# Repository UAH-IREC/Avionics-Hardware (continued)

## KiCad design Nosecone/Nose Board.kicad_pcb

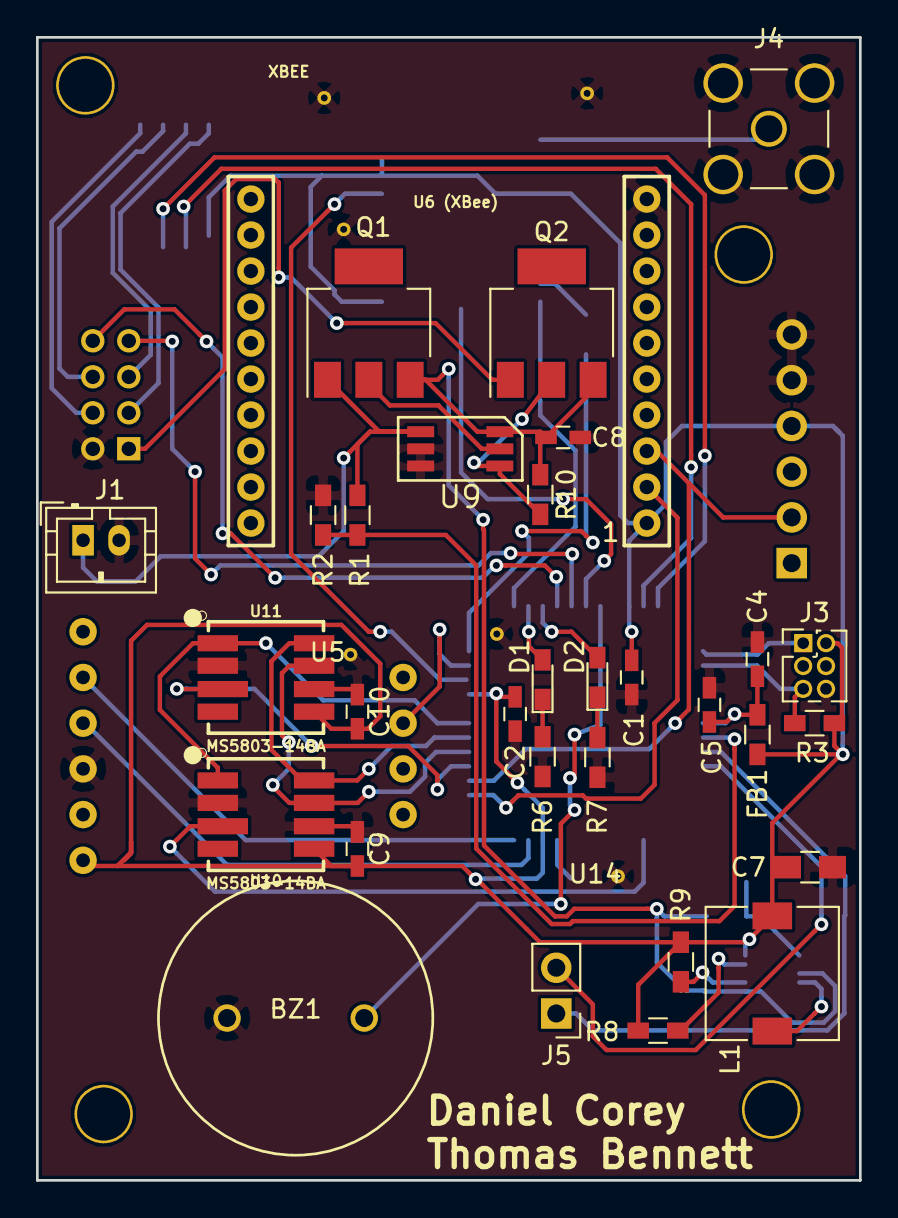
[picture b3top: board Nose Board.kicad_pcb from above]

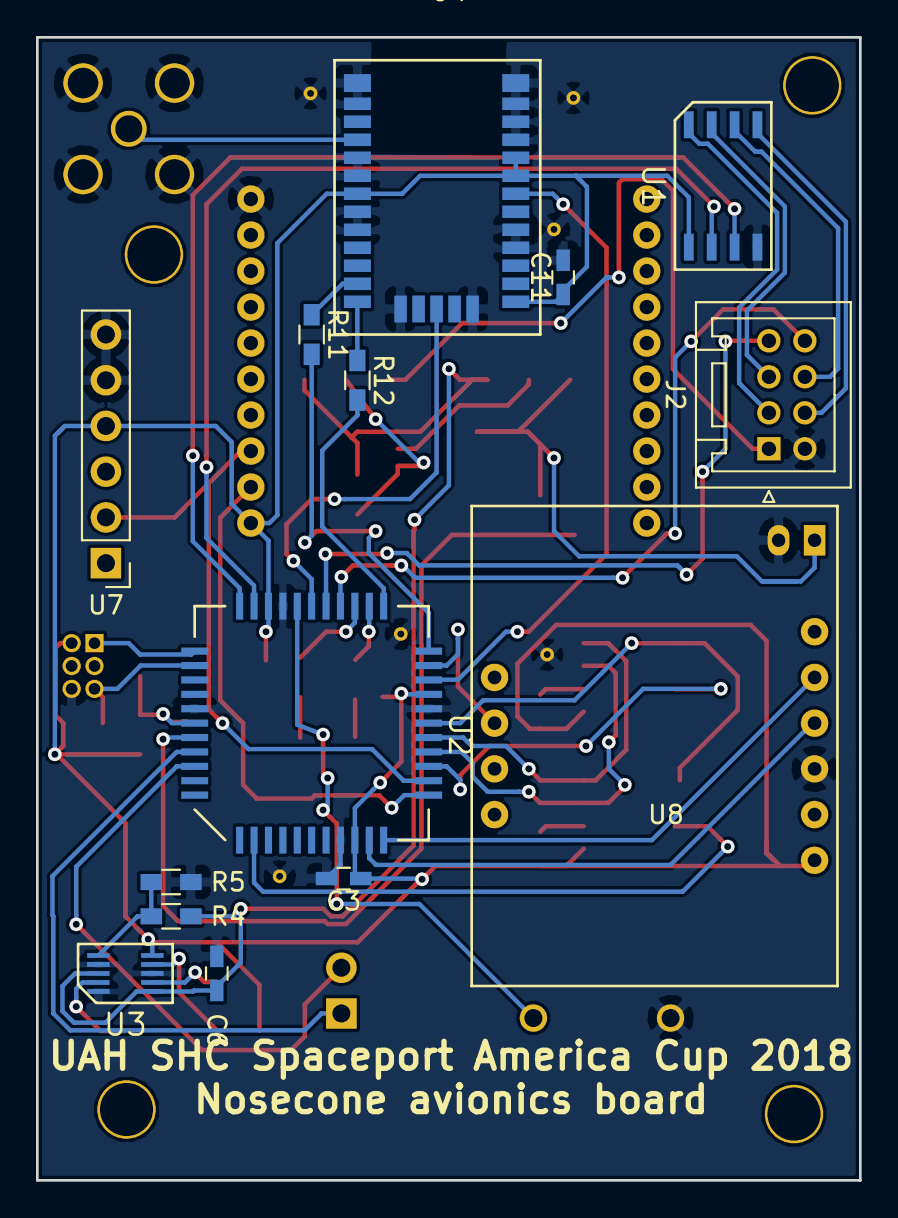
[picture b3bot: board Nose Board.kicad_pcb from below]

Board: 2 copper layers, 45.7 x 63.5 mm, 47 parts (14 on the bottom side), 47 nets.

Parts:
BZ1: Buzzer; Buzzer-CUI_CEP-2242
C1, C2, C3, C5, C9, C10: 100nF; C_0603_HandSoldering
C4, C6: 10uF; C_0603_HandSoldering
C7: 22uF; C_0805_HandSoldering
C8: 22uF; C_0603_HandSoldering
C11: 4.7uF; C_0603_HandSoldering
D1, D2: LED; LED_0603_HandSoldering
FB1: FERRITE_BEAD-0603; L_0603_HandSoldering
J1: Conn_01x02; JST_PH_B2B-PH-K_02x2.00mm_Straight
J2: Conn_02x04_Odd_Even; JST_PUD_B08B-PUDSS_2x04x2.00mm_Straight
J3: Conn_02x03_Odd_Even; Pin_Header_Straight_2x03_Pitch1.27mm
J4: Conn_Coaxial; SMA_THT_Jack_Straight
J5: Conn_01x02; Pin_Header_Straight_1x02_Pitch2.54mm
L1: 10uH; L_7.3x7.3_H4.5
Q1, Q2: Q_PMOS_DGS; SOT-223-3_TabPin2
R1: 90.9k; R_0603_HandSoldering
R2, R3: 10k; R_0603_HandSoldering
R4: 130k; R_0603_HandSoldering
R5: 100k; R_0603_HandSoldering
R6, R7, R11, R12: 220; R_0603_HandSoldering
R8, R9: 1M; R_0603_HandSoldering
R10: 470k; R_0603_HandSoldering
U1: RS485_converter_ISL83488; SOIC-8
U2: ATXMEGA16A4U-AU; QFP_44
U3: 3.3V_DCDC_Conv_TPS62056DGS; SOIC-10
U4: GPS_UBX_CAM_M8C; UBX_CAM-M8C
U5, U14: Via-stitch; Small-via
U6 (XBee): XBEE
U7: OpenLog; Pin_Header_Straight_1x06_Pitch2.54mm
U8: BNO055; BNO055_Breakout
U9: LTC4412; SOIC-6
U10, U11: MS5803-14BA; MS5803

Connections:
+3V3: C1.2, C2.1, C3.1, C7.1, C9.2, C10.2, C11.1, FB1.1, J3.2, L1.1, R3.1, R8.1, R9.1, U1.1, U2.9, U2.19, U2.31, U3.5, U4.1, U4.8, U4.9, U4.20, U6 (XBee).1, U7.4, U8.1, U10.5, U11.5
+BATT: J1.1, Q1.1, R1.1, U9.1
/A1: J5.1, U2.41
/A2: J5.2, U2.42
/Buzzer_drive: BZ1.1, U2.29
/Center_Din: U1.3, U2.33
/Center_Dout: U1.2, U2.32
/Debug_RX: J2.8, U2.26
/Debug_TX: J2.7, U2.27
/GPS1_EXTINT: U2.20, U4.7
/GPS1_PPS: U2.28, U4.29
/GPS1_RXD: R12.2, U2.23
/GPS1_TXD: R11.2, U2.22
/IMU_INT: U2.21, U8.8
/IMU_SCL: U2.11, U8.5
/IMU_SDA: U2.10, U8.4
/LED_STATUS1: D1.2, U2.24
/LED_STATUS2: D2.2, U2.25
/P1_CS: U2.14, U11.3
/P2_CS: U2.2, U10.3
/PDI_CLK: J3.5, R3.2, U2.35
/PDI_Data: J3.1, U2.34
/P_MISO: U2.16, U10.8, U11.8
/P_MOSI: U2.15, U10.7, U11.7
/P_SCLK: U2.17, U10.1, U11.1
/RS422in+: J2.6, U1.6
/RS422in-: J2.4, U1.5
/RS422out+: J2.3, U1.8
/RS422out-: J2.5, U1.7
/Vbatt_meas: R1.2, R2.1, U2.40
/XBEE_Din: U2.13, U6 (XBee).3, U7.2
/XBEE_Dout: U2.12, U6 (XBee).2
GND: BZ1.2, C1.1, C2.2, C3.2, C4.1, C5.1, C6.2, C7.2, C8.2, C9.1, C10.1, C11.2, J1.2, J2.2, J3.6, J4.2, R2.2, R5.2, R6.1, R7.1, U1.4, U2.8, U2.18, U2.30, U2.38, U3.3, U3.7, U3.10, U4.4, U4.5, U4.10, U4.11, U4.12, U4.13, U4.14, U4.15, U4.18, U4.19, U4.21, U4.22, U4.27, U4.31, U5.1, U6 (XBee).10, U7.5, U7.6, U8.3, U9.2, U9.3, U10.2, U10.6, U11.2, U11.6, U14.1
unnamed: C4.2, C5.2, FB1.2, U2.39
unnamed: D1.1, R6.2
unnamed: D2.1, R7.2
unnamed: J4.1, U4.17
unnamed: L1.2, U3.9
unnamed: Q1.2, U9.5
unnamed: Q2.2, R10.2, U9.4
unnamed: R4.2, R5.1, U3.6
unnamed: R8.2, U3.4
unnamed: R9.2, U3.2
unnamed: R11.1, U4.25
unnamed: R12.1, U4.26
VBUS: J2.1, Q2.1
VDC: C6.1, C8.1, Q1.3, Q2.3, R4.1, R10.1, U3.1, U3.8, U9.6

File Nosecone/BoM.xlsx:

Ref | Value | Footprint | Description | Vendor Part Number | Link
BZ1 | Buzzer | Misc components:Buzzer-CUI_CEP-2242 | AUDIO PIEZO INDICATOR 3-16V TH |  | https://www.digikey.com/product-detail/en/cui-inc/CEP-2242/1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
C1 | 100nF | Capacitors_SMD:C_0603_HandSoldering | CAP CER 0.1UF 50V X7R 0603 | 399-7845-1-ND | https://www.digikey.com/product-detail/en/kemet/C0603C104M5R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
C2 | 100nF | Capacitors_SMD:C_0603_HandSoldering | CAP CER 0.1UF 50V X7R 0604 | 399-7845-1-ND | https://www.digikey.com/product-detail/en/kemet/C0603C104M5R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
C3 | 100nF | Capacitors_SMD:C_0603_HandSoldering | CAP CER 0.1UF 50V X7R 0605 | 399-7845-1-ND | https://www.digikey.com/product-detail/en/kemet/C0603C104M5R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
C4 | 10uF | Capacitors_SMD:C_0603_HandSoldering | CAP CER 10UF 35V X5R 0603 | 490-13248-1-ND | https://www.digikey.com/product-detail/en/murata-electronics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
C5 | 100nF | Capacitors_SMD:C_0603_HandSoldering | CAP CER 0.1UF 50V X7R 0605 | 399-7845-1-ND | https://www.digikey.com/product-detail/en/kemet/C0603C104M5R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
C6 | 10uF | Capacitors_SMD:C_0603_HandSoldering | CAP CER 10UF 35V X5R 0603 | 490-13248-1-ND | https://www.digikey.com/product-detail/en/murata-electronics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
C7 | 22uF | Capacitors_SMD:C_0603_HandSoldering | CAP CER 22UF 25V X5R 0805 | 490-12389-1-ND | https://www.digikey.com/product-detail/en/murata-electronics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
C8 | 22uF | Capacitors_SMD:C_0603_HandSoldering | CAP CER 22UF 25V X5R 0805 | 490-12389-1-ND | https://www.digikey.com/product-detail/en/murata-electronics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
C9 | 100nF | Capacitors_SMD:C_0603_HandSoldering | CAP CER 0.1UF 50V X7R 0605 | 399-7845-1-ND | https://www.digikey.com/product-detail/en/kemet/C0603C104M5R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
C10 | 100nF | Capacitors_SMD:C_0603_HandSoldering | CAP CER 0.1UF 50V X7R 0605 | 399-7845-1-ND | https://www.digikey.com/product-detail/en/kemet/C0603C104M5R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
C11 | 4.7uF | Capacitors_SMD:C_0603_HandSoldering | CAP CER 4.7UF 25V X5R 0603 | 1276-1903-1-ND | https://www.digikey.com/product-detail/en/samsung-electro-me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
D1 | LED | LEDs:LED_0603_HandSoldering | LED GREEN CLEAR 0603 SMD | 160-1446-1-ND | https://www.digikey.com/product-detail/en/lite-on-inc/LTST-C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
D2 | LED | LEDs:LED_0603_HandSoldering | LED RED CLEAR 0603 SMD | 160-1447-1-ND | https://www.digikey.com/product-detail/en/lite-on-inc/LTST-C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
FB1 | FERRITE_BEAD-0603 | Inductors_SMD:L_0603_HandSoldering
J1 | Conn_01x02 | Connectors_JST:JST_PH_B2B-PH-K_02x2.00mm_Straight
J2 | Conn_02x04_Odd_Even | Connectors_JST:JST_PUD_B08B-PUDSS_2x04x2.00mm_Straight
J3 | Conn_02x03_Odd_Even | Pin_Headers:Pin_Header_Straight_2x03_Pitch1.27mm
J4 | Conn_Coaxial | Connectors:SMA_THT_Jack_Straight
J5 | Conn_01x02 | Pin_Headers:Pin_Header_Straight_1x02_Pitch2.54mm
L1 | 10uH | Inductors_SMD:L_7.3x7.3_H4.5
Q1 | Q_PMOS_DGS | TO_SOT_Packages_SMD:SOT-223-3_TabPin2 | MOSFET P-CH 60V 7A SOT223 | DMP6023LE-13DICT-ND | https://www.digikey.com/product-detail/en/diodes-incorporate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
Q2 | Q_PMOS_DGS | TO_SOT_Packages_SMD:SOT-223-3_TabPin2 | MOSFET P-CH 60V 7A SOT223 | DMP6023LE-13DICT-ND | https://www.digikey.com/product-detail/en/diodes-incorporate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
R1 | 10k | Resistors_SMD:R_0603_HandSoldering | RES SMD 10K OHM 5% 1/10W 0603 | 311-10KGRCT-ND | https://www.digikey.com/product-detail/en/yageo/RC0603JR-071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
R2 | 90.9k | Resistors_SMD:R_0603_HandSoldering | RES SMD 90.9K OHM 1% 1/10W 0603 | 311-90.9KHRCT-ND | https://www.digikey.com/product-detail/en/yageo/RC0603FR-079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
R3 | 10k | Resistors_SMD:R_0603_HandSoldering | RES SMD 10K OHM 5% 1/10W 0603 | 311-10KGRCT-ND | https://www.digikey.com/product-detail/en/yageo/RC0603JR-071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
R4 | 130k | Resistors_SMD:R_0603_HandSoldering | RES SMD 130K OHM 5% 1/10W 0603 | 311-130KGRCT-ND | https://www.digikey.com/product-detail/en/yageo/RC0603JR-071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
R5 | 100k | Resistors_SMD:R_0603_HandSoldering | RES SMD 100K OHM 5% 1/10W 0603 | CR0603-JW-104ELFCT-ND | https://www.digikey.com/product-detail/en/bourns-inc/CR0603-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
R6 | 220 | Resistors_SMD:R_0603_HandSoldering | RES SMD 220 OHM 5% 1/10W 0603 | 311-220GRCT-ND | https://www.digikey.com/product-detail/en/yageo/RC0603JR-072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
R7 | 220 | Resistors_SMD:R_0603_HandSoldering | RES SMD 220 OHM 5% 1/10W 0603 | 311-220GRCT-ND | https://www.digikey.com/product-detail/en/yageo/RC0603JR-072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
R8 | 1M | Resistors_SMD:R_0603_HandSoldering | RES SMD 1M OHM 1% 1/10W 0603 | 311-1.00MHRCT-ND | https://www.digikey.com/product-detail/en/yageo/RC0603FR-071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
R9 | 1M | Resistors_SMD:R_0603_HandSoldering | RES SMD 1M OHM 1% 1/10W 0604 | 311-1.00MHRCT-ND | https://www.digikey.com/product-detail/en/yageo/RC0603FR-071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
R10 | 470k | Resistors_SMD:R_0603_HandSoldering | RES SMD 470K OHM 5% 1/10W 0603 | 311-470KGRCT-ND | https://www.digikey.com/product-detail/en/yageo/RC0603JR-074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
R11 | 220 | Resistors_SMD:R_0603_HandSoldering | RES SMD 220 OHM 5% 1/10W 0603 | 311-220GRCT-ND | https://www.digikey.com/product-detail/en/yageo/RC0603JR-072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
R12 | 220 | Resistors_SMD:R_0603_HandSoldering | RES SMD 220 OHM 5% 1/10W 0603 | 311-220GRCT-ND | https://www.digikey.com/product-detail/en/yageo/RC0603JR-072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
U1 | RS485_converter_ISL83488 | Misc components:SOIC-8 | IC TXRX RS485/422 3.3V LP 8SOIC | ISL83488IBZ-TCT-ND | https://www.digikey.com/product-detail/en/intersil/ISL83488I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
U2 | ATXMEGA16A4U-AU | Misc components:QFP_44 | IC MCU 8BIT 128KB FLASH 44TQFP | ATXMEGA128A4U-AU-ND | https://www.digikey.com/product-detail/en/microchip-technolo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
U3 | 3.3V_DCDC_Conv_TPS62056DGS | Misc components:SOIC-10 | IC REG BCK 3.3V 0.8A SYNC 10MSOP | 296-27024-1-ND | https://www.digikey.com/product-detail/en/texas-instruments/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
U4 | GPS_UBX_CAM_M8C | Misc components:UBX_CAM-M8C | IC RECEIVER GPS CHIP ANT 31LCC | 672-1014-1-ND | https://www.digikey.com/product-detail/en/u-blox-america-inc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
U5 | Via-stitch | Misc components:Small-via | N/A | N/A | N/A
U6 | XBEE | RF:XBEE | 900 mHz SMA connector | Club stock (for now) | Club stock (for now)
U7 | OpenLog | Pin_Headers:Pin_Header_Straight_1x06_Pitch2.54mm | OPENLOG | 1568-1368-ND | https://www.digikey.com/products/en?mpart=DEV-13712&v=1568
U8 | BNO055 | Misc components:BNO055_Breakout | BREAKOUT BOARD 9-DOF IMU BNO055 | 1528-1426-ND | https://www.digikey.com/products/en?mpart=2472&v=1528
U9 | LTC4412 | Misc components:SOIC-6 | IC OR CTRLR SRC SELECT TSOT23-6 | LTC4412ES6#TRMPBFCT-ND | https://www.digikey.com/product-detail/en/linear-technology/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
U10 | MS5803-14BA | Silicon-Standard:MS5803 | MINIATURE ALTIMETER MODULE | 223-1626-5-ND | https://www.digikey.com/product-detail/en/te-connectivity-me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
U11 | MS5803-14BA | Silicon-Standard:MS5803 | MINIATURE ALTIMETER MODULE | 223-1626-5-ND | https://www.digikey.com/product-detail/en/te-connectivity-me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
U12 | Via-stitch | Misc components:Small-via | N/A | N/A | N/A
U13 | Via-stitch | Misc components:Small-via | N/A | N/A | N/A
N/A | GPS antenna |  |  |  | https://www.digikey.com/product-detail/en/taoglas-limited/AG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
N/A | UFL to SMA adapter
N/A | Breakaway pin headers 0.1" pitch
N/A | Xbee headers
N/A | Female pin headers 0.1" pitch

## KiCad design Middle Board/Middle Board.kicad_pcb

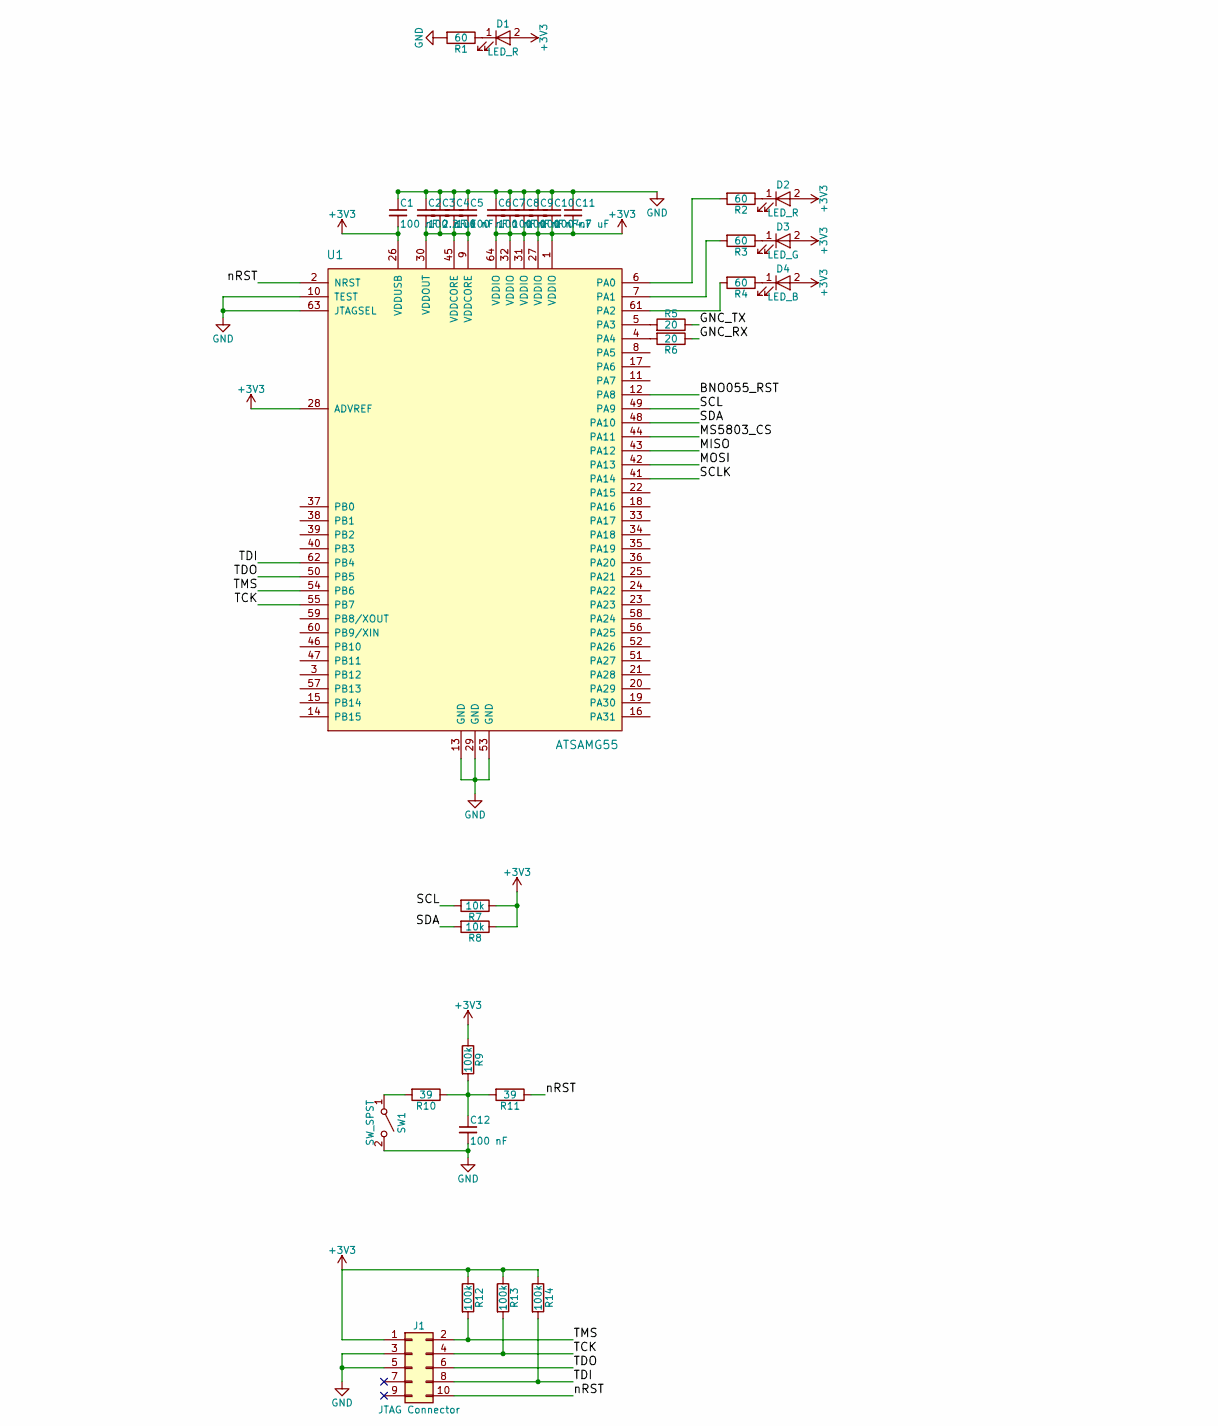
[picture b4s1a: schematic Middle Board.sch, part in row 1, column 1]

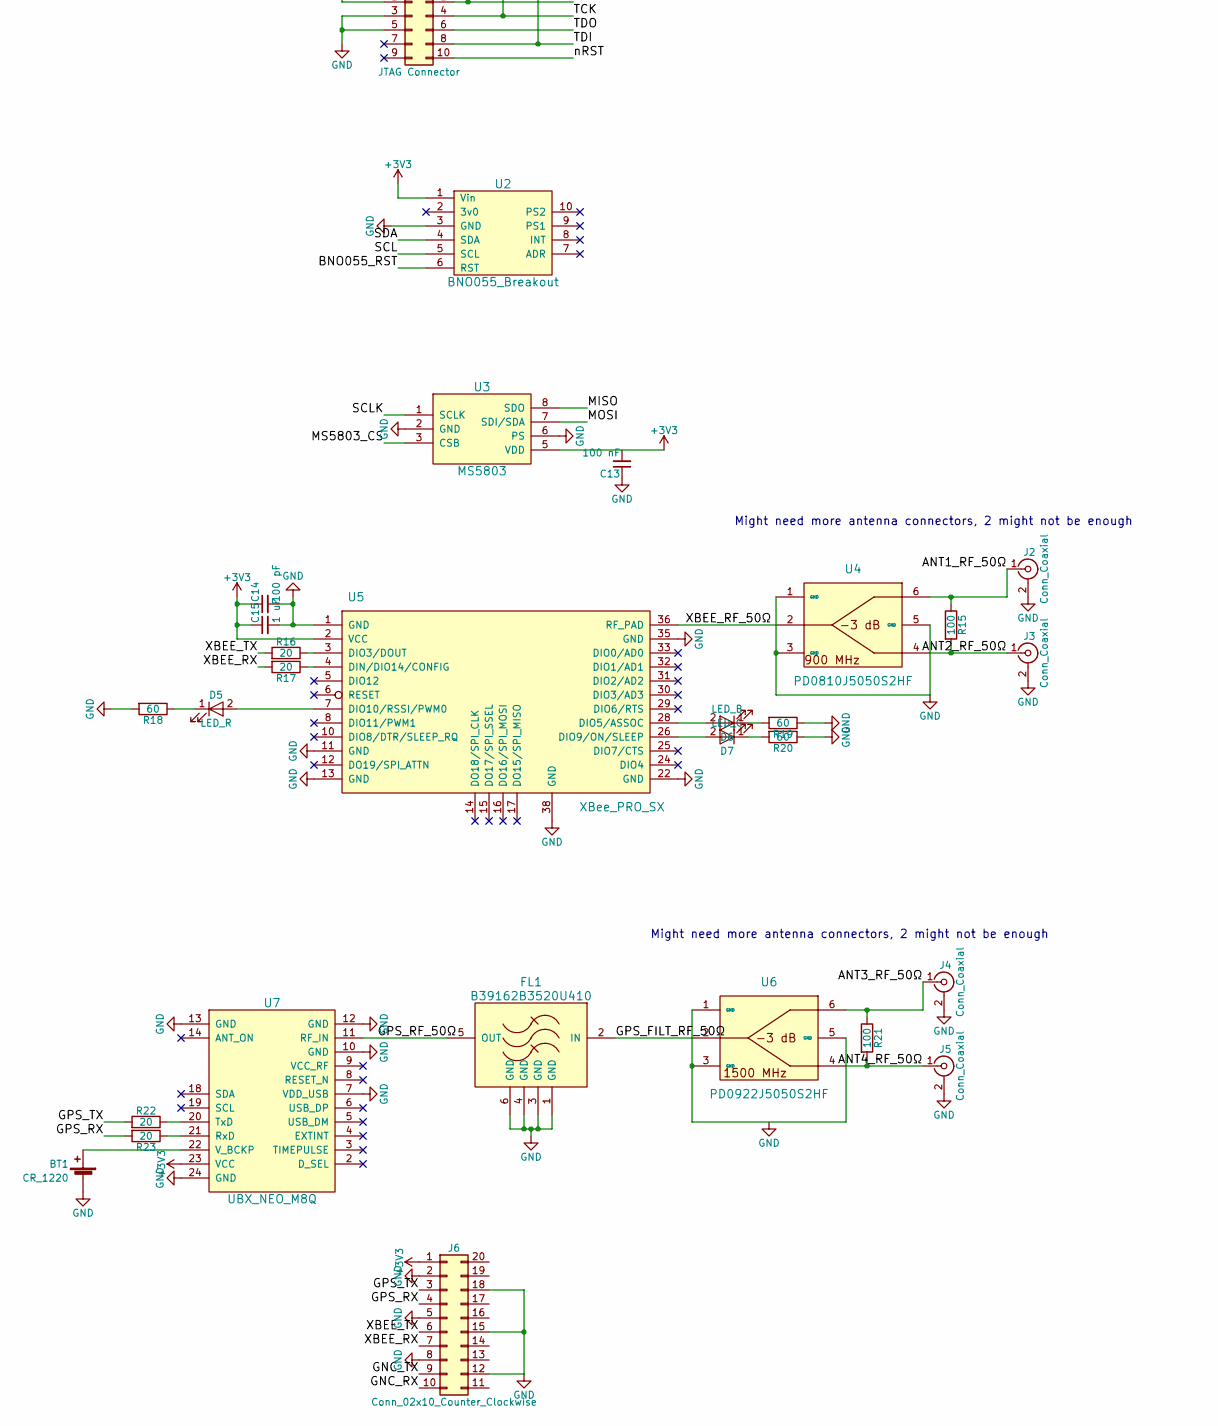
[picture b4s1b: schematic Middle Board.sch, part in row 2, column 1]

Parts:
BT1: CR_1220; Keystone_3000_1x12mm-CoinCell; Digikey Part Number 36-3000-ND
C1, C2, C4, C5, C6, C7, C8, C9, C10, C12, C13: 100 nF; C_0603; Digikey Part Number 490-1532-1-ND
C3: 2.2 uF; C_0603; Digikey Part Number 1276-1134-1-ND
C11: 4.7 uF; C_0805; Digikey Part Number 587-2990-6-ND
C14: 100 pF; C_0603; Digikey Part Number 1276-1909-6-ND
C15: 1 uF; C_0603; Digikey Part Number 1276-6524-1-ND
D1, D2, D5: LED_R; LED_0603_HandSoldering; Digikey Part Number 160-1436-1-ND
D3, D7: LED_G; LED_0603_HandSoldering; Digikey Part Number 160-1435-1-ND
D4, D6: LED_B; LED_0603_HandSoldering; Digikey Part Number 160-1647-1-ND
FL1: B39162B3520U410; Digikey Part Number 495-2363-6-ND
J1: JTAG Connector; 10_pin_Cortex-M_connector; Digikey Part Number SAM8799-ND
J2, J3, J4, J5: Conn_Coaxial; SMA_SMD_RIGHT_ANGLE; Digikey Part Number 931-1175-ND
J6: Conn_02x10_Counter_Clockwise; CONN_CARD_02x10_MALE; Digikey Part Number S3299-ND
R1, R2, R3, R4, R18, R19, R20: 60; R_0603; Digikey Part Number 311-56GRCT-ND
R5, R6, R16, R17, R22, R23: 20; R_0603; Digikey Part Number 311-20.0HRCT-ND
R7, R8: 10k; R_0603; Digikey Part Number 311-10.0KHRCT-ND
R9, R12, R13, R14: 100k; R_0603; Digikey Part Number 311-100KHRCT-ND
R10, R11: 39; R_0603; Digikey Part Number 311-39.0HRCT-ND
R15, R21: 100; R_0603; Digikey Part Number P100DBDKR-ND
SW1: SW_SPST; SW_SPST_SMD; Digikey Part Number CKN9112CT-ND
U1: ATSAMG55; LQFP-64_10x10mm_Pitch0.5mm; Digikey Part Number ATSAMG55J19B-AUTCT-ND
U2: BNO055_Breakout; Digikey Part Number 1528-1426-ND
U3: MS5803; Digikey Part Number 223-1623-5-ND
U4: PD0810J5050S2HF; SMD_PD_ANAREN; Digikey Part Number 1173-1093-1-ND
U5: XBee_PRO_SX; XBEE_PRO_SX; Digikey Part Number 602-1889-ND
U6: PD0922J5050S2HF; SMD_PD_ANAREN; Digikey Part Number 1173-1094-1-ND
U7: UBX_NEO_M8Q; Digikey Part Number 672-1009-1-ND

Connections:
+3V3: C1.2, C6.2, C7.2, C8.2, C9.2, C10.2, C11.2, C14.1, C15.1, D1.2 (A), D2.2 (A), D3.2 (A), D4.2 (A), J1.1, J6.1, R7.1, R8.1, R9.1, R12.1, R13.1, R14.1, U1.1 (VDDIO), U1.26 (VDDUSB), U1.27 (VDDIO), U1.28 (ADVREF), U1.31 (VDDIO), U1.32 (VDDIO), U1.64 (VDDIO), U2.1 (Vin), U3.5 (VDD), U5.2 (VCC), U7.23 (VCC)
/ANT1_RF_50Ω: J2.1 (In), R15.1, U4.6
/ANT2_RF_50Ω: J3.1 (In), R15.2, U4.4
/ANT3_RF_50Ω: J4.1 (In), R21.1, U6.6
/ANT4_RF_50Ω: J5.1 (In), R21.2, U6.4
/BNO055_RST: U1.12 (PA8), U2.6 (RST)
/GNC_RX: J6.10, R6.1
/GNC_TX: J6.9, R5.1
/GPS_FILT_RF_50Ω: FL1.2 (IN), U6.2
/GPS_RF_50Ω: FL1.5 (OUT), U7.11 (RF_IN)
/GPS_RX: J6.4, R23.2
/GPS_TX: J6.3, R22.2
/MISO: U1.43 (PA12), U3.8 (SDO)
/MOSI: U1.42 (PA13), U3.7 (SDI/SDA)
/MS5803_CS: U1.44 (PA11), U3.3 (CSB)
/SCL: R7.2, U1.49 (PA9), U2.5 (SCL)
/SCLK: U1.41 (PA14), U3.1 (SCLK)
/SDA: R8.2, U1.48 (PA10), U2.4 (SDA)
/TCK: J1.4, R13.2, U1.55 (PB7)
/TDI: J1.8, R14.2, U1.62 (PB4)
/TDO: J1.6, U1.50 (PB5)
/TMS: J1.2, R12.2, U1.54 (PB6)
/XBEE_RF_50Ω: U4.2, U5.36 (RF_PAD)
/XBEE_RX: J6.7, R17.2
/XBEE_TX: J6.6, R16.2
/nRST: J1.10, R11.1, U1.2 (NRST)
GND: BT1.2 (-), C1.1, C2.1, C3.1, C4.1, C5.1, C6.1, C7.1, C8.1, C9.1, C10.1, C11.1, C12.2, C13.1, C14.2, C15.2, FL1.1 (GND), FL1.3 (GND), FL1.4 (GND), FL1.6 (GND), J1.3, J1.5, J2.2 (Ext), J3.2 (Ext), J4.2 (Ext), J5.2 (Ext), J6.2, J6.5, J6.8, J6.12, J6.15, J6.18, R1.2, R18.2, R19.1, R20.1, SW1.2 (B), U1.10 (TEST), U1.13 (GND), U1.29 (GND), U1.53 (GND), U1.63 (JTAGSEL), U2.3 (GND), U3.2 (GND), U3.6 (PS), U4.1 (GND), U4.3 (GND), U4.5 (GND), U5.1 (GND), U5.11 (GND), U5.13 (GND), U5.22 (GND), U5.35 (GND), U5.38 (GND), U6.1 (GND), U6.3 (GND), U6.5 (GND), U7.7 (VDD_USB), U7.10 (GND), U7.12 (GND), U7.13 (GND), U7.24 (GND)
unnamed: BT1.1 (+), U7.22 (V_BCKP)
unnamed: C2.2, C3.2, C4.2, C5.2, U1.9 (VDDCORE), U1.30 (VDDOUT), U1.45 (VDDCORE)
unnamed: C12.1, R9.2, R10.1, R11.2
unnamed: D1.1 (K), R1.1
unnamed: D2.1 (K), R2.1
unnamed: D3.1 (K), R3.1
unnamed: D4.1 (K), R4.1
unnamed: D5.1 (K), R18.1
unnamed: D5.2 (A), U5.7 (DIO10/RSSI/PWM0)
unnamed: D6.1 (K), R19.2
unnamed: D6.2 (A), U5.28 (DIO5/ASSOC)
unnamed: D7.1 (K), R20.2
unnamed: D7.2 (A), U5.26 (DIO9/ON/SLEEP)
unnamed: R2.2, U1.6 (PA0)
unnamed: R3.2, U1.7 (PA1)
unnamed: R4.2, U1.61 (PA2)
unnamed: R5.2, U1.5 (PA3)
unnamed: R6.2, U1.4 (PA4)
unnamed: R10.2, SW1.1 (A)
unnamed: R16.1, U5.3 (DIO3/DOUT)
unnamed: R17.1, U5.4 (DIN/DIO14/CONFIG)
unnamed: R22.1, U7.20 (TxD)
unnamed: R23.1, U7.21 (RxD)

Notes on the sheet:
Might need more antenna connectors, 2 might not be enough

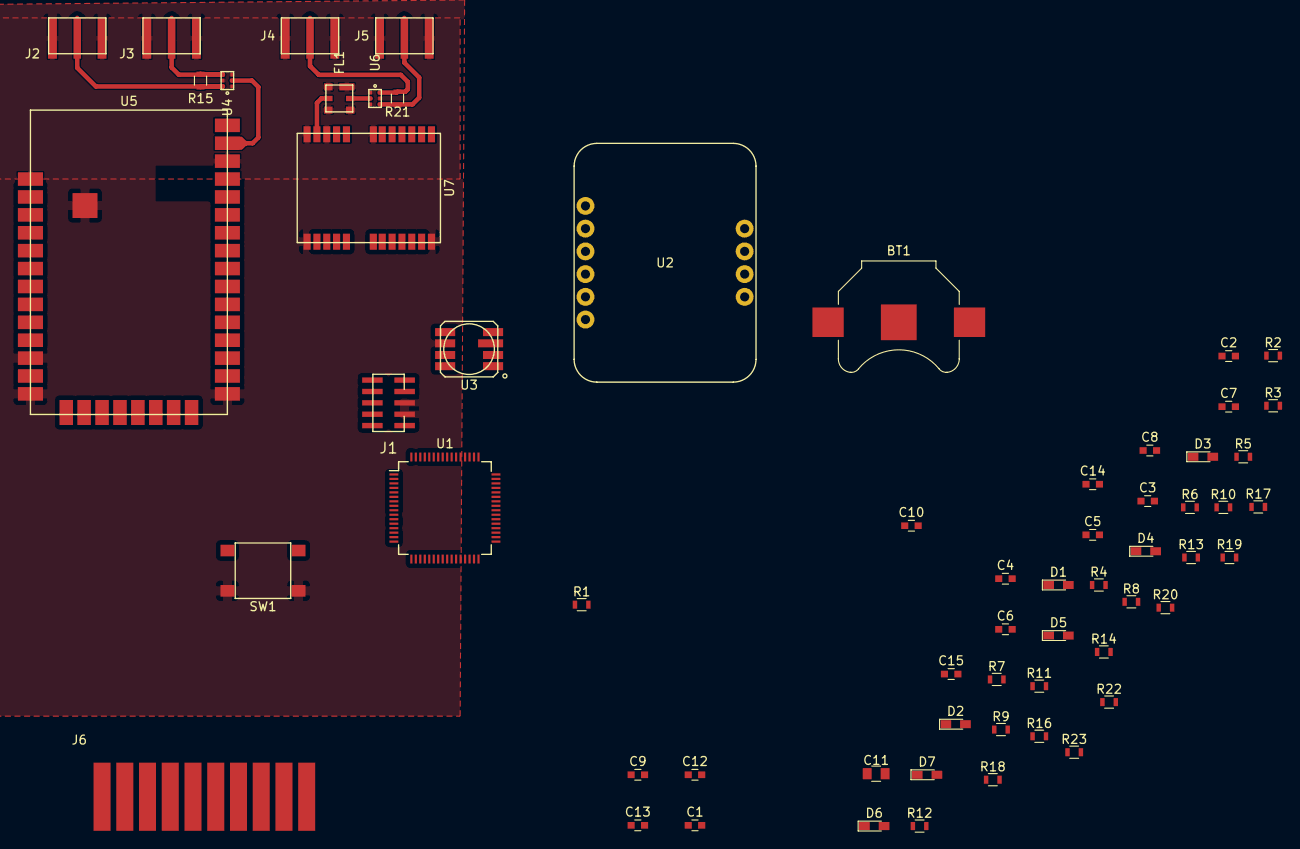
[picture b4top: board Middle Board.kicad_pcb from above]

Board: 2 copper layers, 61 parts (0 on the bottom side), 50 nets.

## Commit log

2017-12-18 Library components
2017-12-18 Library upload
2017-12-18 Moved to correct folder
2017-12-18 Initial library upload
2017-12-18 Created nose cone schematic file
2017-12-18 Couple little things before I give up for the night
2017-12-18 Added components, some nets
2017-12-19 Added more components to schematic
2017-12-19 Started inserting smaller circuit components
2017-12-19 Schematic complete, pending review
2017-12-19 Added pressure sensors, began routing
2017-12-19 Continued routing
2017-12-19 Placement adjustments
2017-12-23 PCB Routed
2017-12-24 Minor board adjustments, BoM work
2017-12-26 Layout/BoM adjustments
    Known annular ring size problems, will fix those soon-ish
2017-12-27 Actually fixed the DRC issues. Oops
2017-12-28 Better routing
2017-12-28 Fixed via sizes, I think
2017-12-28 Actually fixed via sizes, I think
2017-12-28 I think it's done now
2018-01-15 Fixed via and board outline issues
2018-01-28 Started on middle board
2018-01-28 Finished GNC section schematic
    Still need to find digikey part numbers
2018-01-29 Added XBee to Mainboard
2018-01-29 Added GPS to mainboard schematic
    Went with a different GPS module than the one Daniel picked out since
    we're going with external antennas
2018-01-29 Small changes
2018-01-29 Apparently I forgot to save everything earlier
2018-01-29 Forgot ground in power dividers
2018-01-30 Added digikey part numbers and a utility to mass edit fields
2018-01-30 Added some footprints
2018-01-31 More Middle Board Footprints
2018-02-01 Finished middle board footprints
    PCB Time!
2018-02-01 Started on PCB
2018-02-07 More changes
2018-02-11 New project for control board
    also added TC measurement stuff
2018-02-11 PT and TC read circuits, assigned MCU pins
2018-02-11 More small changes
2018-02-11 Added misc stuff, only thing left is power system
2018-02-21 Added the RS422 transceiver since I forgot it
2018-02-27 Finished Control Board Schematic
2018-02-27 Added digikey part numbers to all components in control board
2018-02-28 Minor Stuff
2018-02-28 Added a lot of footprints
2018-02-28 Reviewed and corrected built in footprints
2018-02-28 More built-in component fixing
2018-02-28 More Footprints
2018-02-28 Last Footprint
2018-03-01 Started control board PCB
2018-03-01 Routed Or Controller
2018-03-01 More routing
2018-03-04 Split power board into its own PCB
2018-03-04 Removed power supply from control board
2018-03-05 Removed buzzer, changed board sizes
2018-03-06 Finished routing power board
2018-03-06 Fixed a few little things
2018-03-06 Ready for power PCB review
    Also added a kick-ass logo to the backside
2018-03-06 Updated some clearances and sizes
2018-03-06 BOM Stuff
2018-03-06 Made the edge connector GND connections wider
    Also a few minor cosmetic changes
2018-03-07 Updated power board to kicad 5
2018-03-07 Forgot an openlog on the control board
    Had to get rid of the fault detect pins on the TCs, will have to poll for faults over SPI now
2018-03-08 Last commit before I change the board shape
2018-03-09 New Board shape
    Thanks a lot James
2018-03-13 A whole lot of changes
    Kinda forgot what they all were
2018-03-14 Starting to make control board match power board
2018-03-15 Added a quick and dirty hotfire schematic
2018-03-15 Updated control board schematic
2018-03-15 Added footprints to new stuff on control board
2018-03-15 Added digikey part numbers
2018-03-17 Routed a ton of stuff on the control board
2018-03-20 Added comments and stuff for power board PCB review
2018-08-22 Started implementing battery charger/balancer, upgraded to KiCad 5 stable
2018-08-23 Finished battery charger schematic
    still need to fill out BOM, and start cell balancer
2018-08-27 Finished Balancer and charger schematic
    Still need to change umbilical voltage input range
2018-08-29 Did some digikey part number replacing
2018-10-08 Finally getting ready to work again
2018-10-08 Added Heatsink, changed umbilical voltage
    10.5 volts is technically above the max reccomended supply for the lipo balancer, but it's set to that to make sure the supply doesn't come in and out if it's at 10 volts
2018-10-10 Few changes
2018-10-10 Changed power board monitoring strategy
    Now has onboard MCU
2018-10-14 Schematic done (again)
    Still needs footprints and part numbers
2018-11-03 Removed Voltage sensing from main board, added 2 PTs
2018-11-03 Actually making the changes in the last commit because I forgot to save first
2018-11-03 Added VCC_IN back to the header
    I forgot the control board still needs it
2018-11-03 Changed to 2x7 header from 2x10
2018-11-03 Removed openlog breakout, duplicated openlog
    I copied the schematic from https://github.com/sparkfun/OpenLog/tree/master/hardware. This was done to save some vertical space, since headers are pretty tall. It should also be more robust.
2018-11-03 Remembered to add connectors for the new PTs
2018-11-03 Removed servo control MOSFETs
    Now connected directly. They can work with a 3.3v PWM signal according to https://www.servocity.com/hs-m7990th-servo
2018-11-03 Added some series resistors to the servo control lines
2018-11-03 Started Hotfire Comms Board Project
2018-11-03 Hotfire comms schematic basically done
2018-11-03 Added safety radio to control board
    Uses LoRa, which is has a lower data rate than XBees, but much longer range for a given power consumption. Should be able to reach 6000 ft with low gain antennas. It's also way cheaper.
2018-11-03 Actually saved the file this time
2018-11-03 Create Safing Remote Project
2018-11-03 Added a few components to safing remote
2018-11-05 Finished Safing Remote Schematic
2018-11-05 Little change
2018-11-06 Started annotating, fixed a few errors
2018-11-06 Annotated Power Board Schematic
2018-11-06 Finished annotating
2018-11-12 Power Board Part Numbers and Easy Footprints
2018-11-13 Added KiBOM, started work on control board
2018-11-14 Fixed Library stuff
2018-11-14 Added Footprints
    3.3v DC-DC Inductor
    AON7423 P-type MosFET
2018-11-14 Added Footprints
    3.3v DC-DC Inductor
    AON7423 P-type MosFET
    It gave me an error when I tried to commit using Github desktop.
2018-11-14 Linked L1 and Q7 to their footprints
    Meant to do this with earlier commit, oops.
2018-11-16 Reorganization
2018-11-17 Added inductor and connector footprints
    DFE252012C inductor and XT30PW connector footprints
2018-11-17 Started control board part numbering
2018-11-17 Finished Control Board Part Numbers
2018-11-17 Fixed hotfire comms board shematic
2018-11-17 Added FT232RL to hotfire comms board to allow it to be used at AGC end
    AGC = Avionics Ground Station
2018-11-17 *AGS not AGC
2018-11-17 Added some footprints to Hotfire Comms board
2018-11-17 Associated a few control board footprints
2018-11-17 Started on control board footprints
2018-11-22 Remembered static electricity is a thing
2018-11-27 Changed a few things, forgot what they were but I'm sure they're not major
2019-01-12 Started fixing umbilical voltage problem, adding TVS diodes
2019-01-12 Finished Charger Step Up
2019-01-15 Charger load switch
2019-01-16 Added TVS diodes to some critical parts on power board
2019-01-17 Added A footprint
2019-01-17 One more footprint
2019-01-18 Apparently connector footprints are odd-even by default, not counterclockwise
2019-01-18 Power Board Footprints Done!
2019-01-18 Finally ready to redo power PCB
2019-01-19 Switching to a screw terminal for power board
2019-01-19 Screw Terminals 4lyfe
2019-01-19 Made board bigger, started layout
2019-02-14 Started block layout
2019-02-14 Finished grouping components
2019-02-14 Started routing of blocks
2019-02-14 More blocks routed
2019-02-14 Blocks blocks blocks
